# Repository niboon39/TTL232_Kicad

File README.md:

# TTL232_Kicad
TTL232_USB_B_micro

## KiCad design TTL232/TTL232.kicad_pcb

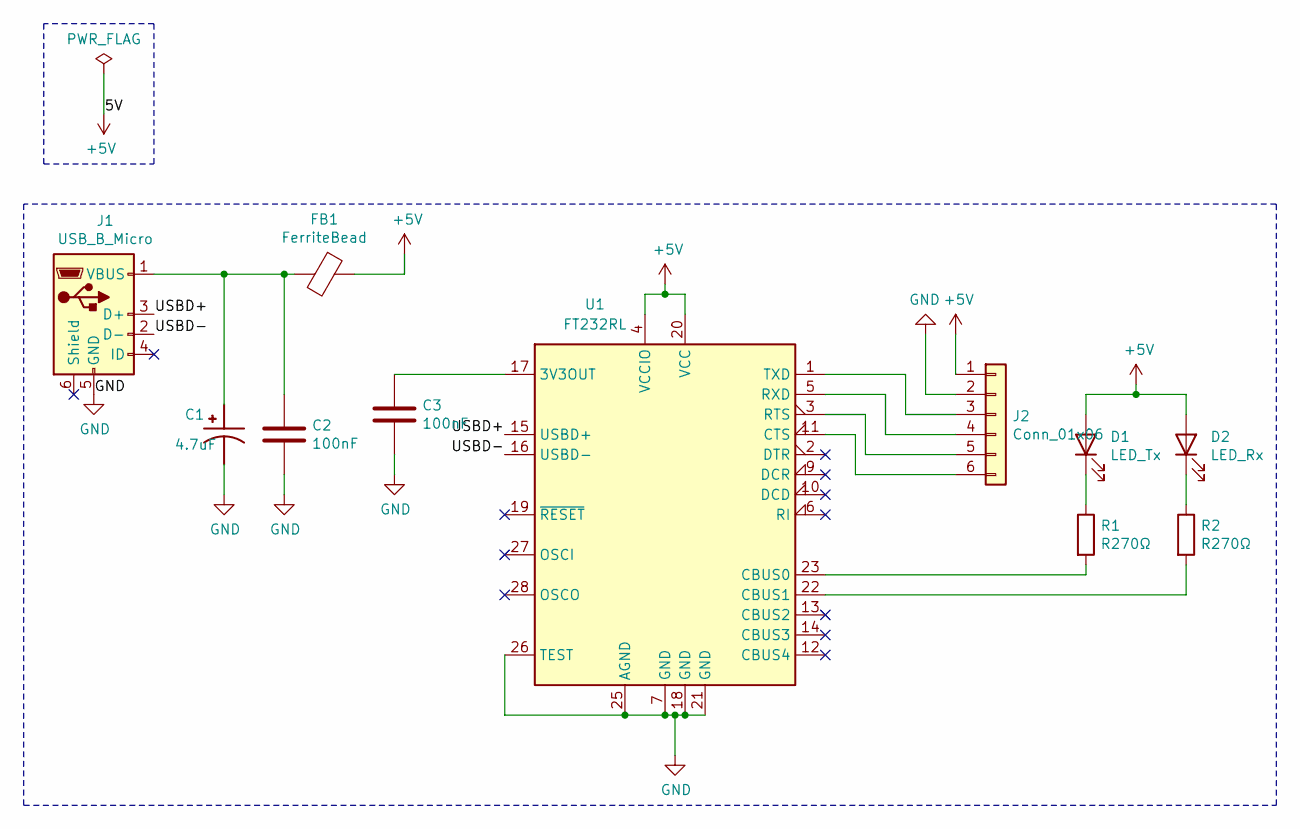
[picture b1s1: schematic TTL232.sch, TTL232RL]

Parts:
C1: 4.7uF; C_0805_2012Metric; PARTREV 20-Dec-19
C2, C3: 100nF; C_0805_2012Metric
D1: LED_Tx; LED_0805_2012Metric
D2: LED_Rx; LED_0805_2012Metric
FB1: FerriteBead; L_0805_2012Metric
J1: USB_B_Micro; USB-MINIB-5pin
J2: Conn_01x06; PinSocket_1x06_P2.00mm_Vertical
R1, R2: R270Ω; R_0805_2012Metric
U1: FT232RL; SSOP-28_5.3x10.2mm_P0.65mm

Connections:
+5V: D1.2 (A), D2.2 (A), FB1.1, J2.1, U1.4 (VCCIO), U1.20 (VCC)
/USBD+: J1.3 (D+), U1.15 (USBD+)
/USBD-: J1.2 (D-), U1.16 (USBD-)
GND: C1.2, C2.2, C3.2, J1.5 (GND), J2.2, U1.7 (GND), U1.18 (GND), U1.21 (GND), U1.25 (AGND), U1.26 (TEST)
unnamed: C1.1, C2.1, FB1.2, J1.1 (VBUS)
unnamed: C3.1, U1.17 (3V3OUT)
unnamed: D1.1 (K), R1.1
unnamed: D2.1 (K), R2.1
unnamed: J2.3, U1.1 (TXD)
unnamed: J2.4, U1.5 (RXD)
unnamed: J2.5, U1.3 (RTS)
unnamed: J2.6, U1.11 (CTS)
unnamed: R1.2, U1.23 (CBUS0)
unnamed: R2.2, U1.22 (CBUS1)

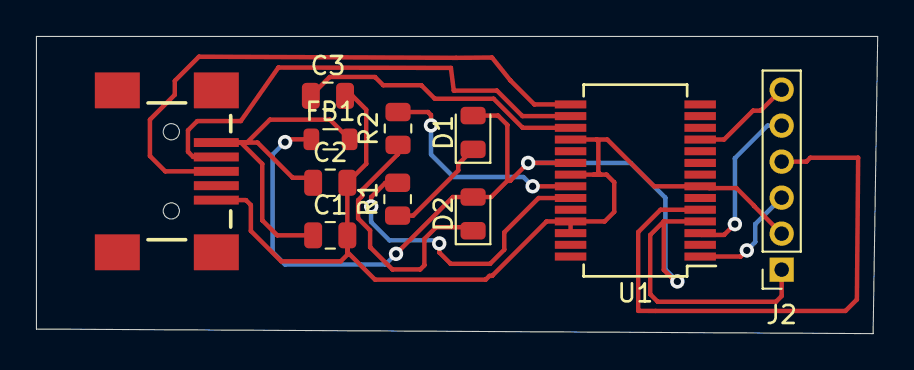
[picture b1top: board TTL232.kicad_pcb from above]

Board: 2 copper layers, 46.7 x 16.5 mm, 11 parts (0 on the bottom side), 14 nets.
